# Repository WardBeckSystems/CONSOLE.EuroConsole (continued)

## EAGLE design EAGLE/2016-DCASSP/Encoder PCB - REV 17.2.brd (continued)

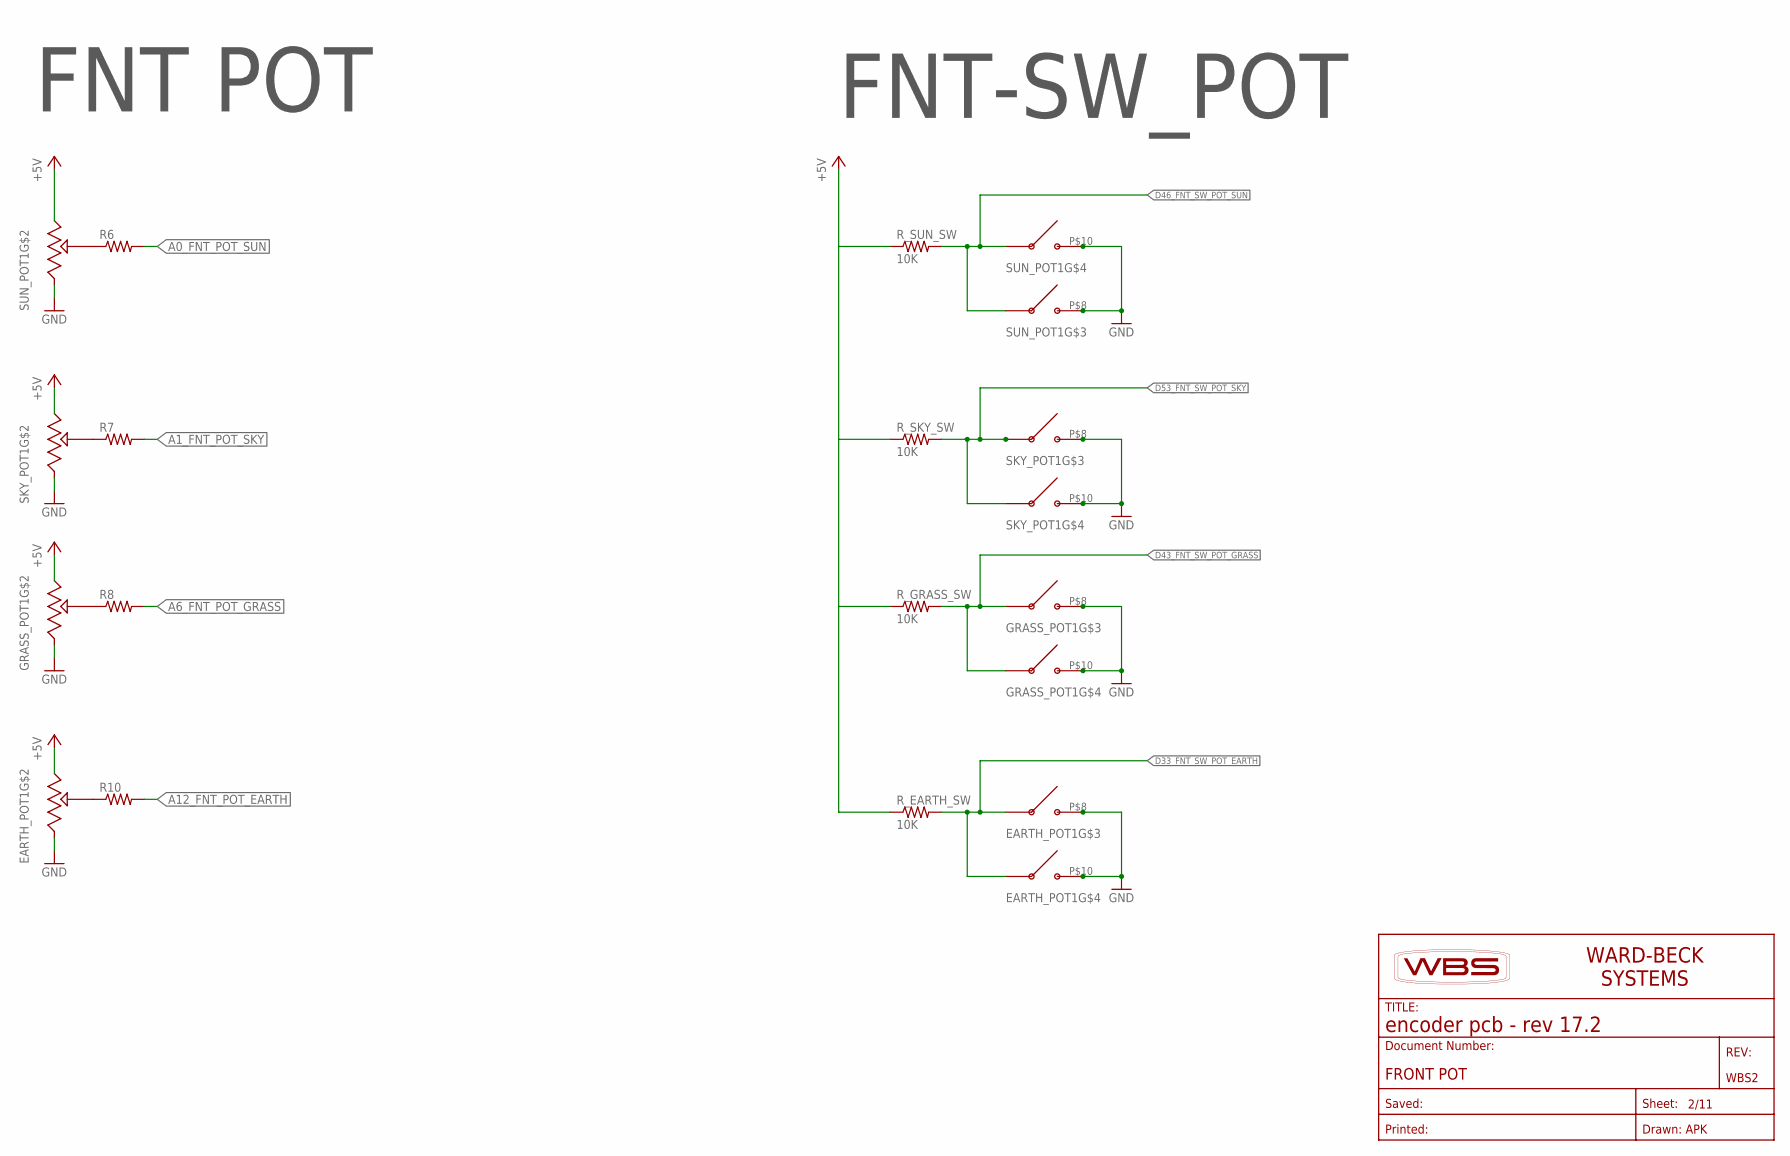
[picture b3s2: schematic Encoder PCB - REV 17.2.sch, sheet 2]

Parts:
EARTH_POT1: WBS_10-081_DUALPOT+DUALSWITCH; WBS_10-081
GRASS_POT1: WBS_10-081_DUALPOT+DUALSWITCH; WBS_10-081
R6, R7, R8, R10: R-US_0309/12; 0309/12
R_EARTH_SW: 10K; M0805
R_GRASS_SW: 10K; M0805
R_SKY_SW: 10K; M0805
R_SUN_SW: 10K; M0805
SKY_POT1: WBS_10-081_DUALPOT+DUALSWITCH; WBS_10-081
SUN_POT1: WBS_10-081_DUALPOT+DUALSWITCH; WBS_10-081
WBS2: FRONT POT; WBS-FRAME_PCB

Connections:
+5V: EARTH_POT1.P$6 (CW), GRASS_POT1.P$6 (CW), R_EARTH_SW.1, R_GRASS_SW.1, R_SKY_SW.1, R_SUN_SW.1, SKY_POT1.P$6 (CW), SUN_POT1.P$6 (CW); also elsewhere on the board
A0_FNT_POT_SUN: R6.2; also elsewhere on the board
A1_FNT_POT_SKY: R7.2; also elsewhere on the board
A6_FNT_POT_GRASS: R8.2; also elsewhere on the board
A12_FNT_POT_EARTH: R10.2; also elsewhere on the board
D33_FNT_SW_POT_EARTH: EARTH_POT1.P$7, EARTH_POT1.P$9, R_EARTH_SW.2; also elsewhere on the board
D43_FNT_SW_POT_GRASS: GRASS_POT1.P$7, GRASS_POT1.P$9, R_GRASS_SW.2; also elsewhere on the board
D46_FNT_SW_POT_SUN: R_SUN_SW.2, SUN_POT1.P$7, SUN_POT1.P$9; also elsewhere on the board
D53_FNT_SW_POT_SKY: R_SKY_SW.2, SKY_POT1.P$7, SKY_POT1.P$9; also elsewhere on the board
GND: EARTH_POT1.P$4 (CCW), EARTH_POT1.P$8, EARTH_POT1.P$10, GRASS_POT1.P$4 (CCW), GRASS_POT1.P$8, GRASS_POT1.P$10, SKY_POT1.P$4 (CCW), SKY_POT1.P$8, SKY_POT1.P$10, SUN_POT1.P$4 (CCW), SUN_POT1.P$8, SUN_POT1.P$10; also elsewhere on the board
unnamed: EARTH_POT1.P$5 (WIPER), R10.1
unnamed: R7.1, SKY_POT1.P$5 (WIPER)
unnamed: R6.1, SUN_POT1.P$5 (WIPER)
unnamed: GRASS_POT1.P$5 (WIPER), R8.1

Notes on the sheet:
FNT POT
FNT-SW_POT

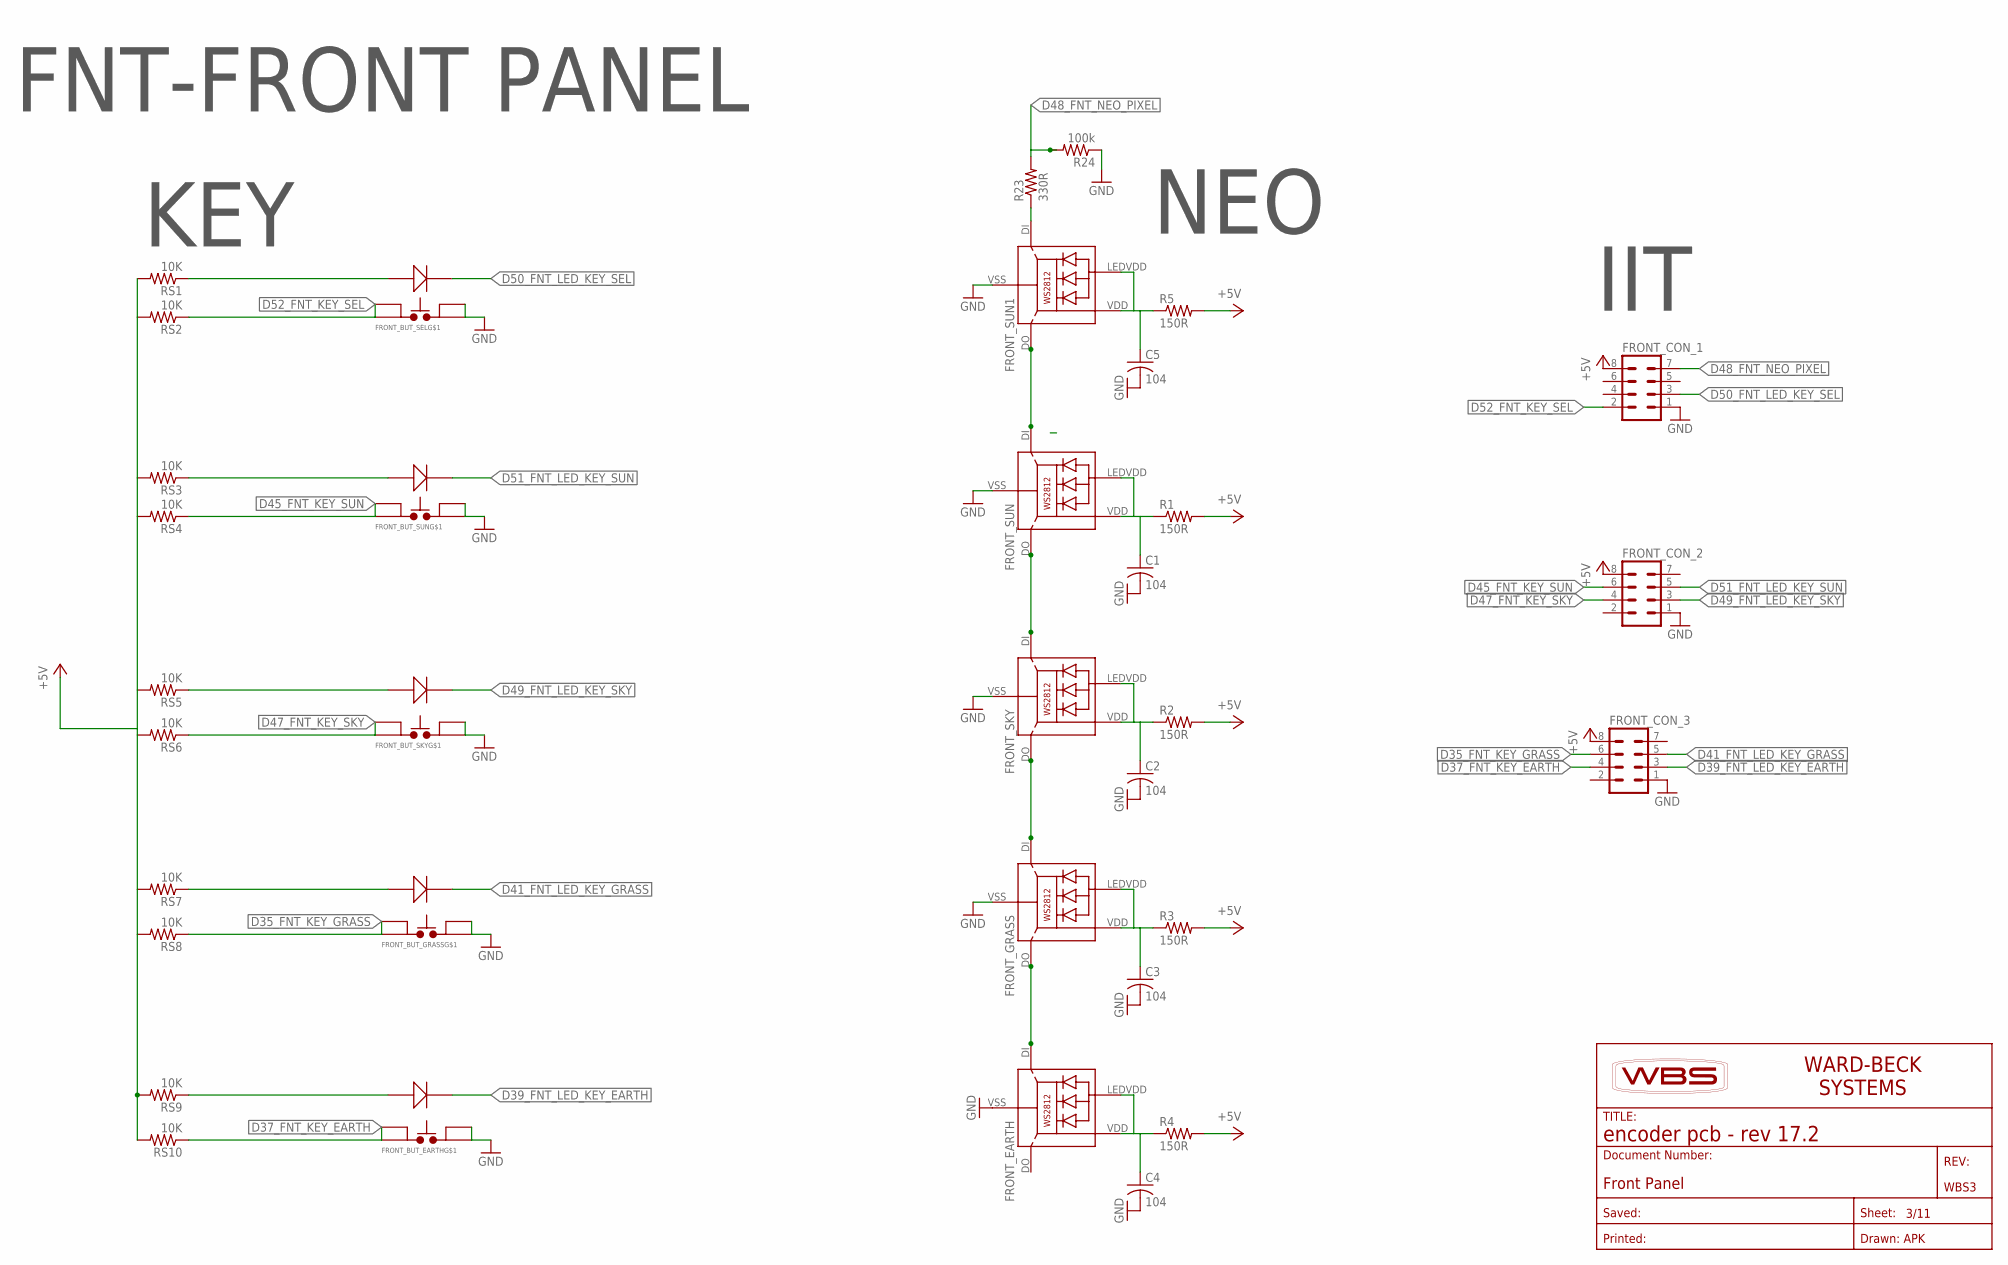
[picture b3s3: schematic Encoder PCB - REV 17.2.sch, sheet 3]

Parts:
C1, C2, C3, C4, C5: 104; C0805
FRONT_BUT_EARTH: SWITCH-POD-BUTTON_WITH_LED; SWITCH-PODBUTTON
FRONT_BUT_GRASS: SWITCH-POD-BUTTON_WITH_LED; SWITCH-PODBUTTON
FRONT_BUT_SEL: SWITCH-POD-BUTTON_WITH_LED; SWITCH-PODBUTTON
FRONT_BUT_SKY: SWITCH-POD-BUTTON_WITH_LED; SWITCH-PODBUTTON
FRONT_BUT_SUN: SWITCH-POD-BUTTON_WITH_LED; SWITCH-PODBUTTON
FRONT_CON_1, FRONT_CON_2, FRONT_CON_3: MA04-2
FRONT_EARTH: WS2812
FRONT_GRASS: WS2812
FRONT_SKY: WS2812
FRONT_SUN, FRONT_SUN1: WS2812
R1, R2, R3, R4, R5: 150R; M0805
R23: 330R; M0805
R24: 100k; M0805
RS1, RS2, RS3, RS4, RS5, RS6, RS7, RS8, RS9, RS10: 10K; M0805
WBS3: Front Panel; WBS-FRAME_PCB

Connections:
+5V: FRONT_CON_1.8, FRONT_CON_2.8, FRONT_CON_3.8, R1.2, R2.2, R3.2, R4.2, R5.2, RS1.2, RS2.2, RS3.2, RS4.2, RS5.2, RS6.2, RS7.2, RS8.2, RS9.2, RS10.2; also elsewhere on the board
D35_FNT_KEY_GRASS: FRONT_BUT_GRASS.SW1A, FRONT_BUT_GRASS.SW2A, FRONT_CON_3.6, RS8.1; also elsewhere on the board
D37_FNT_KEY_EARTH: FRONT_BUT_EARTH.SW1A, FRONT_BUT_EARTH.SW2A, FRONT_CON_3.4, RS10.1; also elsewhere on the board
D39_FNT_LED_KEY_EARTH: FRONT_BUT_EARTH.LEDB, FRONT_CON_3.3; also elsewhere on the board
D41_FNT_LED_KEY_GRASS: FRONT_BUT_GRASS.LEDB, FRONT_CON_3.5; also elsewhere on the board
D45_FNT_KEY_SUN: FRONT_BUT_SUN.SW1A, FRONT_BUT_SUN.SW2A, FRONT_CON_2.6, RS4.1; also elsewhere on the board
D47_FNT_KEY_SKY: FRONT_BUT_SKY.SW1A, FRONT_BUT_SKY.SW2A, FRONT_CON_2.4, RS6.1; also elsewhere on the board
D48_FNT_NEO_PIXEL: FRONT_CON_1.7, R23.2, R24.2; also elsewhere on the board
D49_FNT_LED_KEY_SKY: FRONT_BUT_SKY.LEDB, FRONT_CON_2.3; also elsewhere on the board
D50_FNT_LED_KEY_SEL: FRONT_BUT_SEL.LEDB, FRONT_CON_1.3; also elsewhere on the board
D51_FNT_LED_KEY_SUN: FRONT_BUT_SUN.LEDB, FRONT_CON_2.5; also elsewhere on the board
D52_FNT_KEY_SEL: FRONT_BUT_SEL.SW1A, FRONT_BUT_SEL.SW2A, FRONT_CON_1.2, RS2.1; also elsewhere on the board
GND: C1.2, C2.2, C3.2, C4.2, C5.2, FRONT_BUT_EARTH.SW1B, FRONT_BUT_EARTH.SW2B, FRONT_BUT_GRASS.SW1B, FRONT_BUT_GRASS.SW2B, FRONT_BUT_SEL.SW1B, FRONT_BUT_SEL.SW2B, FRONT_BUT_SKY.SW1B, FRONT_BUT_SKY.SW2B, FRONT_BUT_SUN.SW1B, FRONT_BUT_SUN.SW2B, FRONT_CON_1.1, FRONT_CON_2.1, FRONT_CON_3.1, FRONT_EARTH.VSS (GND), FRONT_GRASS.VSS (GND), FRONT_SKY.VSS (GND), FRONT_SUN.VSS (GND), FRONT_SUN1.VSS (GND), R24.1; also elsewhere on the board
unnamed: FRONT_BUT_GRASS.LEDA, RS7.1
unnamed: FRONT_BUT_SKY.LEDA, RS5.1
unnamed: C1.1, FRONT_SUN.LEDVDD, FRONT_SUN.VDD, R1.1
unnamed: FRONT_BUT_SUN.LEDA, RS3.1
unnamed: FRONT_BUT_SEL.LEDA, RS1.1
unnamed: FRONT_GRASS.DI, FRONT_SKY.DO
unnamed: C2.1, FRONT_SKY.LEDVDD, FRONT_SKY.VDD, R2.1
unnamed: FRONT_BUT_EARTH.LEDA, RS9.1
unnamed: C3.1, FRONT_GRASS.LEDVDD, FRONT_GRASS.VDD, R3.1
unnamed: FRONT_SUN.DI, FRONT_SUN1.DO
unnamed: C4.1, FRONT_EARTH.LEDVDD, FRONT_EARTH.VDD, R4.1
unnamed: C5.1, FRONT_SUN1.LEDVDD, FRONT_SUN1.VDD, R5.1
unnamed: FRONT_EARTH.DI, FRONT_GRASS.DO, FRONT_SKY.DI, FRONT_SUN.DO
unnamed: FRONT_SUN1.DI, R23.1

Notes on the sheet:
FNT-FRONT PANEL
KEY
NEO
IIT

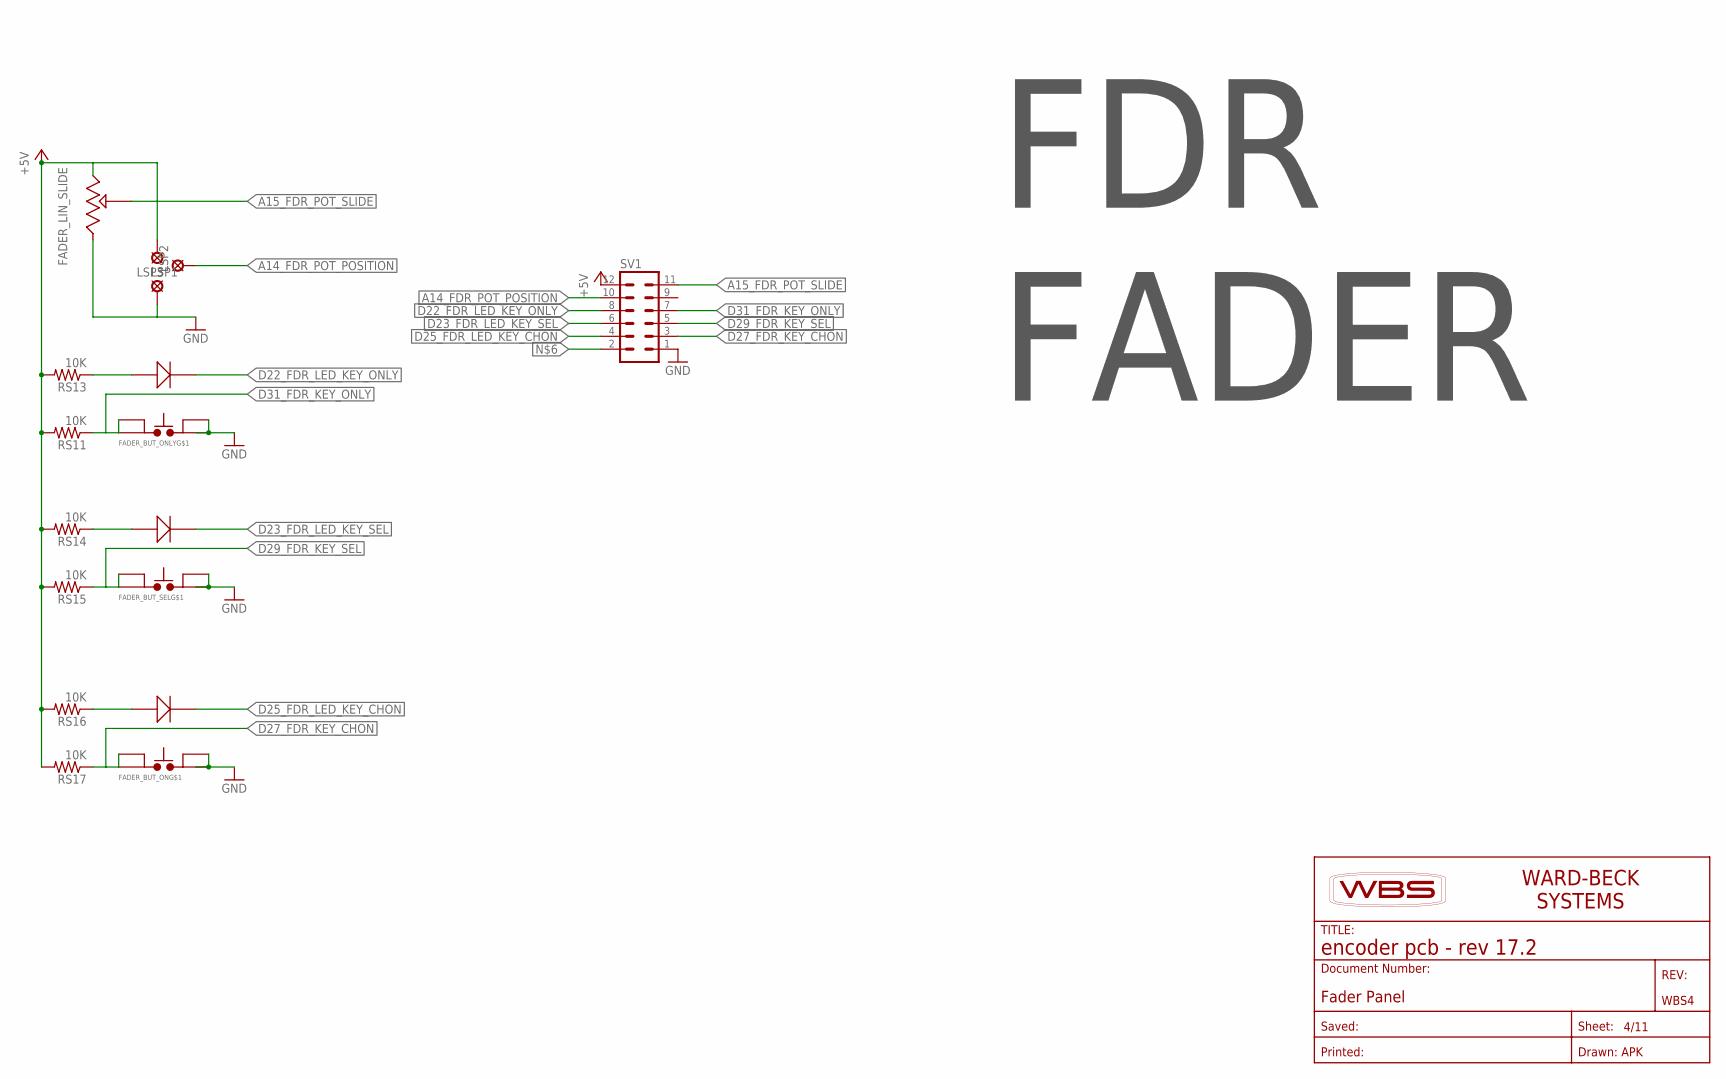
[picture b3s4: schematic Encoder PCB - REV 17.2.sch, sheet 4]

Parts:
FADER_BUT_ON: SWITCH-POD-BUTTON_WITH_LED; SWITCH-PODBUTTON
FADER_BUT_ONLY: SWITCH-POD-BUTTON_WITH_LED; SWITCH-PODBUTTON
FADER_BUT_SEL: SWITCH-POD-BUTTON_WITH_LED; SWITCH-PODBUTTON
FADER_LIN_SLIDE: BOURNS-PTA6043_SLIDEPOT
LSP1, LSP2, LSP3: MCS10B
RS11, RS13, RS14, RS15, RS16, RS17: 10K; M0805
SV1: MA06-2
WBS4: Fader Panel; WBS-FRAME_PCB

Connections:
+5V: FADER_LIN_SLIDE.P$3 (CW), LSP3.MP, RS11.2, RS13.2, RS14.2, RS15.2, RS16.2, RS17.2, SV1.12; also elsewhere on the board
A14_FDR_POT_POSITION: LSP2.MP, SV1.10; also elsewhere on the board
A15_FDR_POT_SLIDE: FADER_LIN_SLIDE.P$2 (WIPER), SV1.11; also elsewhere on the board
D22_FDR_LED_KEY_ONLY: FADER_BUT_ONLY.LEDB, SV1.8; also elsewhere on the board
D23_FDR_LED_KEY_SEL: FADER_BUT_SEL.LEDB, SV1.6; also elsewhere on the board
D25_FDR_LED_KEY_CHON: FADER_BUT_ON.LEDB, SV1.4; also elsewhere on the board
D27_FDR_KEY_CHON: FADER_BUT_ON.SW1A, FADER_BUT_ON.SW2A, RS17.1, SV1.3; also elsewhere on the board
D29_FDR_KEY_SEL: FADER_BUT_SEL.SW1A, FADER_BUT_SEL.SW2A, RS15.1, SV1.5; also elsewhere on the board
D31_FDR_KEY_ONLY: FADER_BUT_ONLY.SW1A, FADER_BUT_ONLY.SW2A, RS11.1, SV1.7; also elsewhere on the board
GND: FADER_BUT_ON.SW1B, FADER_BUT_ON.SW2B, FADER_BUT_ONLY.SW1B, FADER_BUT_ONLY.SW2B, FADER_BUT_SEL.SW1B, FADER_BUT_SEL.SW2B, FADER_LIN_SLIDE.P$1 (CCW), LSP1.MP, SV1.1; also elsewhere on the board
unnamed: FADER_BUT_ON.LEDA, RS16.1
unnamed: FADER_BUT_SEL.LEDA, RS14.1
unnamed: FADER_BUT_ONLY.LEDA, RS13.1
unnamed 67: SV1.2; also elsewhere on the board

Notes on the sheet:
FDR FADER

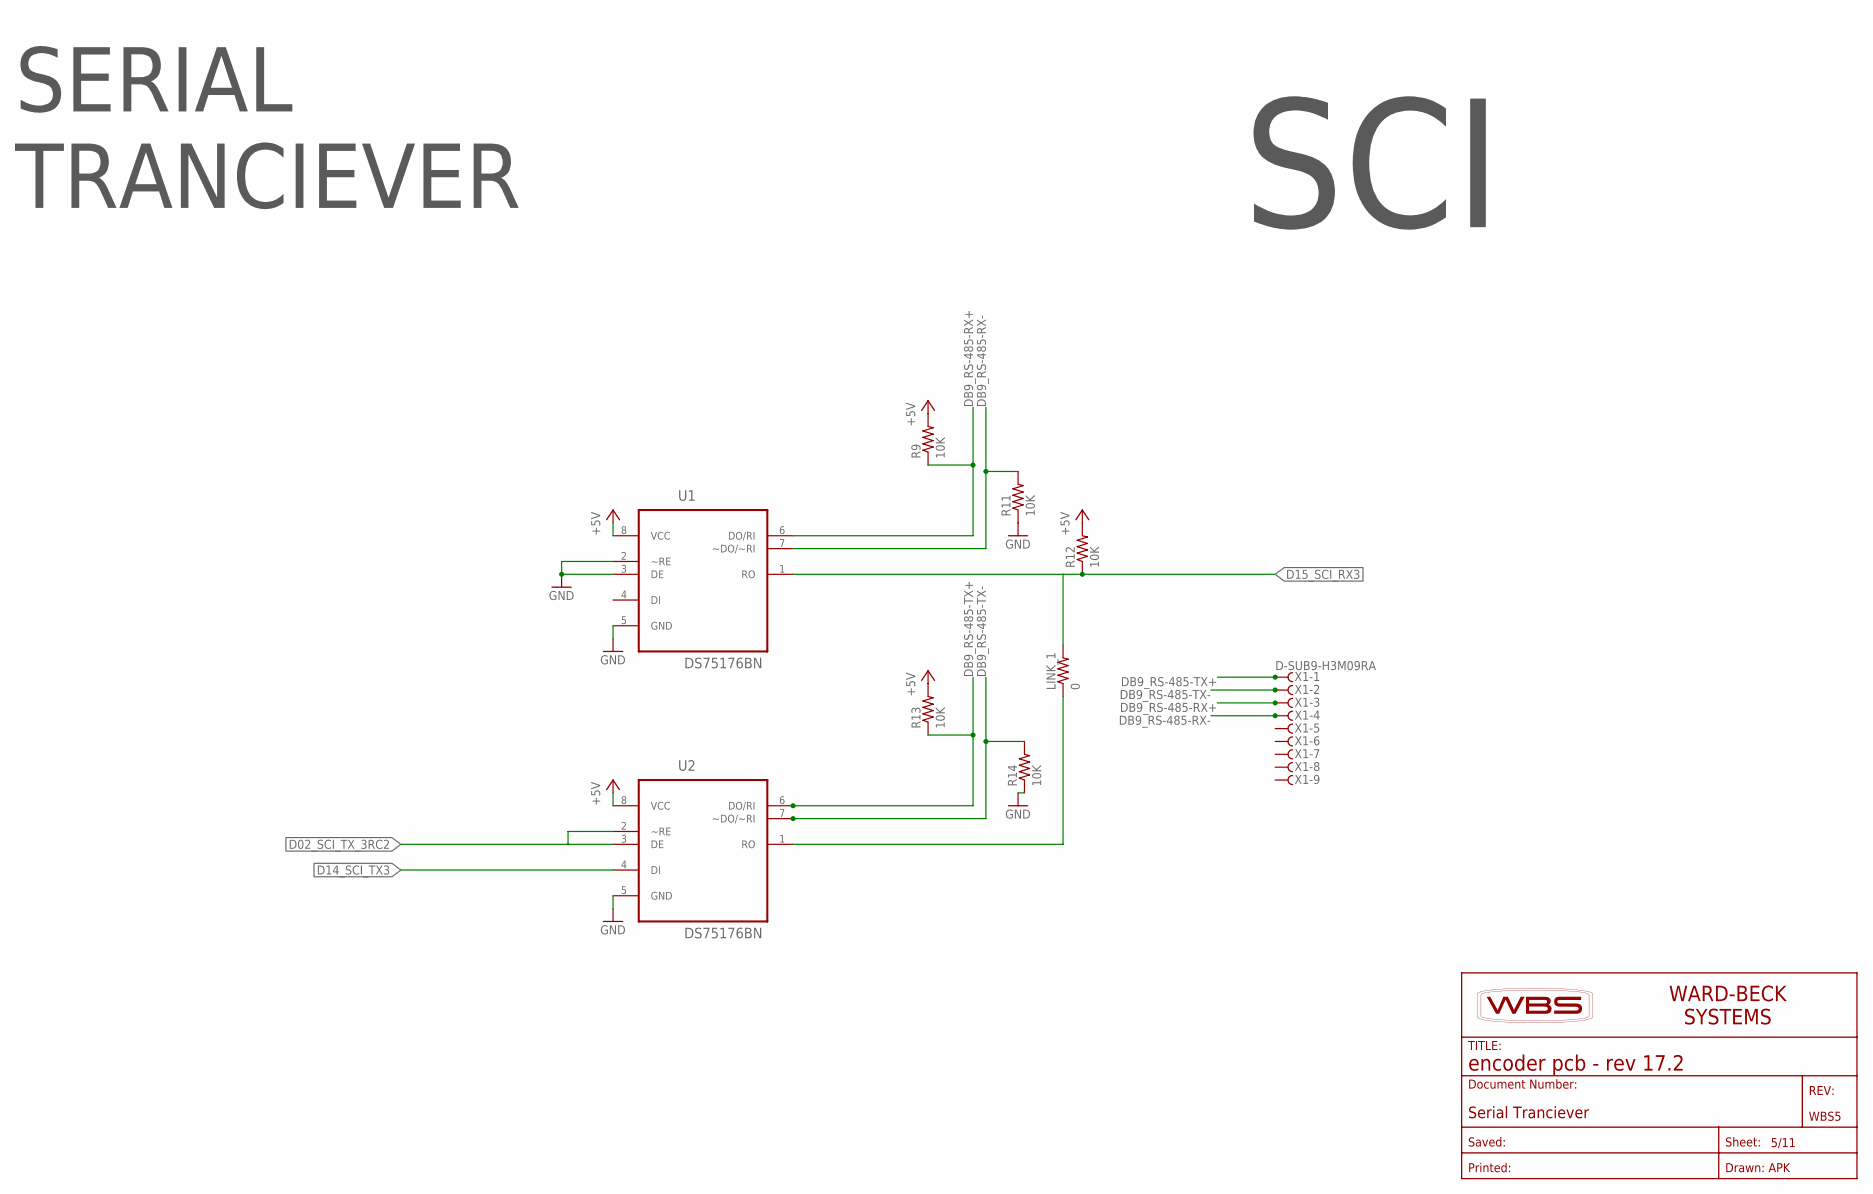
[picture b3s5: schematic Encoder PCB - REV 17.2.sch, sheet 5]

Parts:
LINK_1: 0; M0805
R9, R11, R12, R13, R14: 10K; M0805
U1, U2: DS75176BN; DIP254P762X508-8
WBS5: Serial Tranciever; WBS-FRAME_PCB
X1: D-SUB9-H3M09RA; H3M09RA

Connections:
+5V: R9.2, R12.2, R13.2, U1.8 (VCC), U2.8 (VCC); also elsewhere on the board
D02_SCI_TX_3RC2: U2.2 (~RE), U2.3 (DE); also elsewhere on the board
D14_SCI_TX3: U2.4 (DI); also elsewhere on the board
D15_SCI_RX3: LINK_1.2, R12.1, U1.1 (RO); also elsewhere on the board
DB9_RS-485-RX+: R9.1, U1.6 (DO/RI), X1.3
DB9_RS-485-RX-: R11.2, U1.7 (~DO/~RI), X1.4
DB9_RS-485-TX+: R13.1, U2.6 (DO/RI), X1.1
DB9_RS-485-TX-: R14.2, U2.7 (~DO/~RI), X1.2
GND: R11.1, R14.1, U1.2 (~RE), U1.3 (DE), U1.5 (GND), U2.5 (GND); also elsewhere on the board
unnamed: LINK_1.1, U2.1 (RO)

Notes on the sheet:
SERIAL TRANCIEVER
SCI

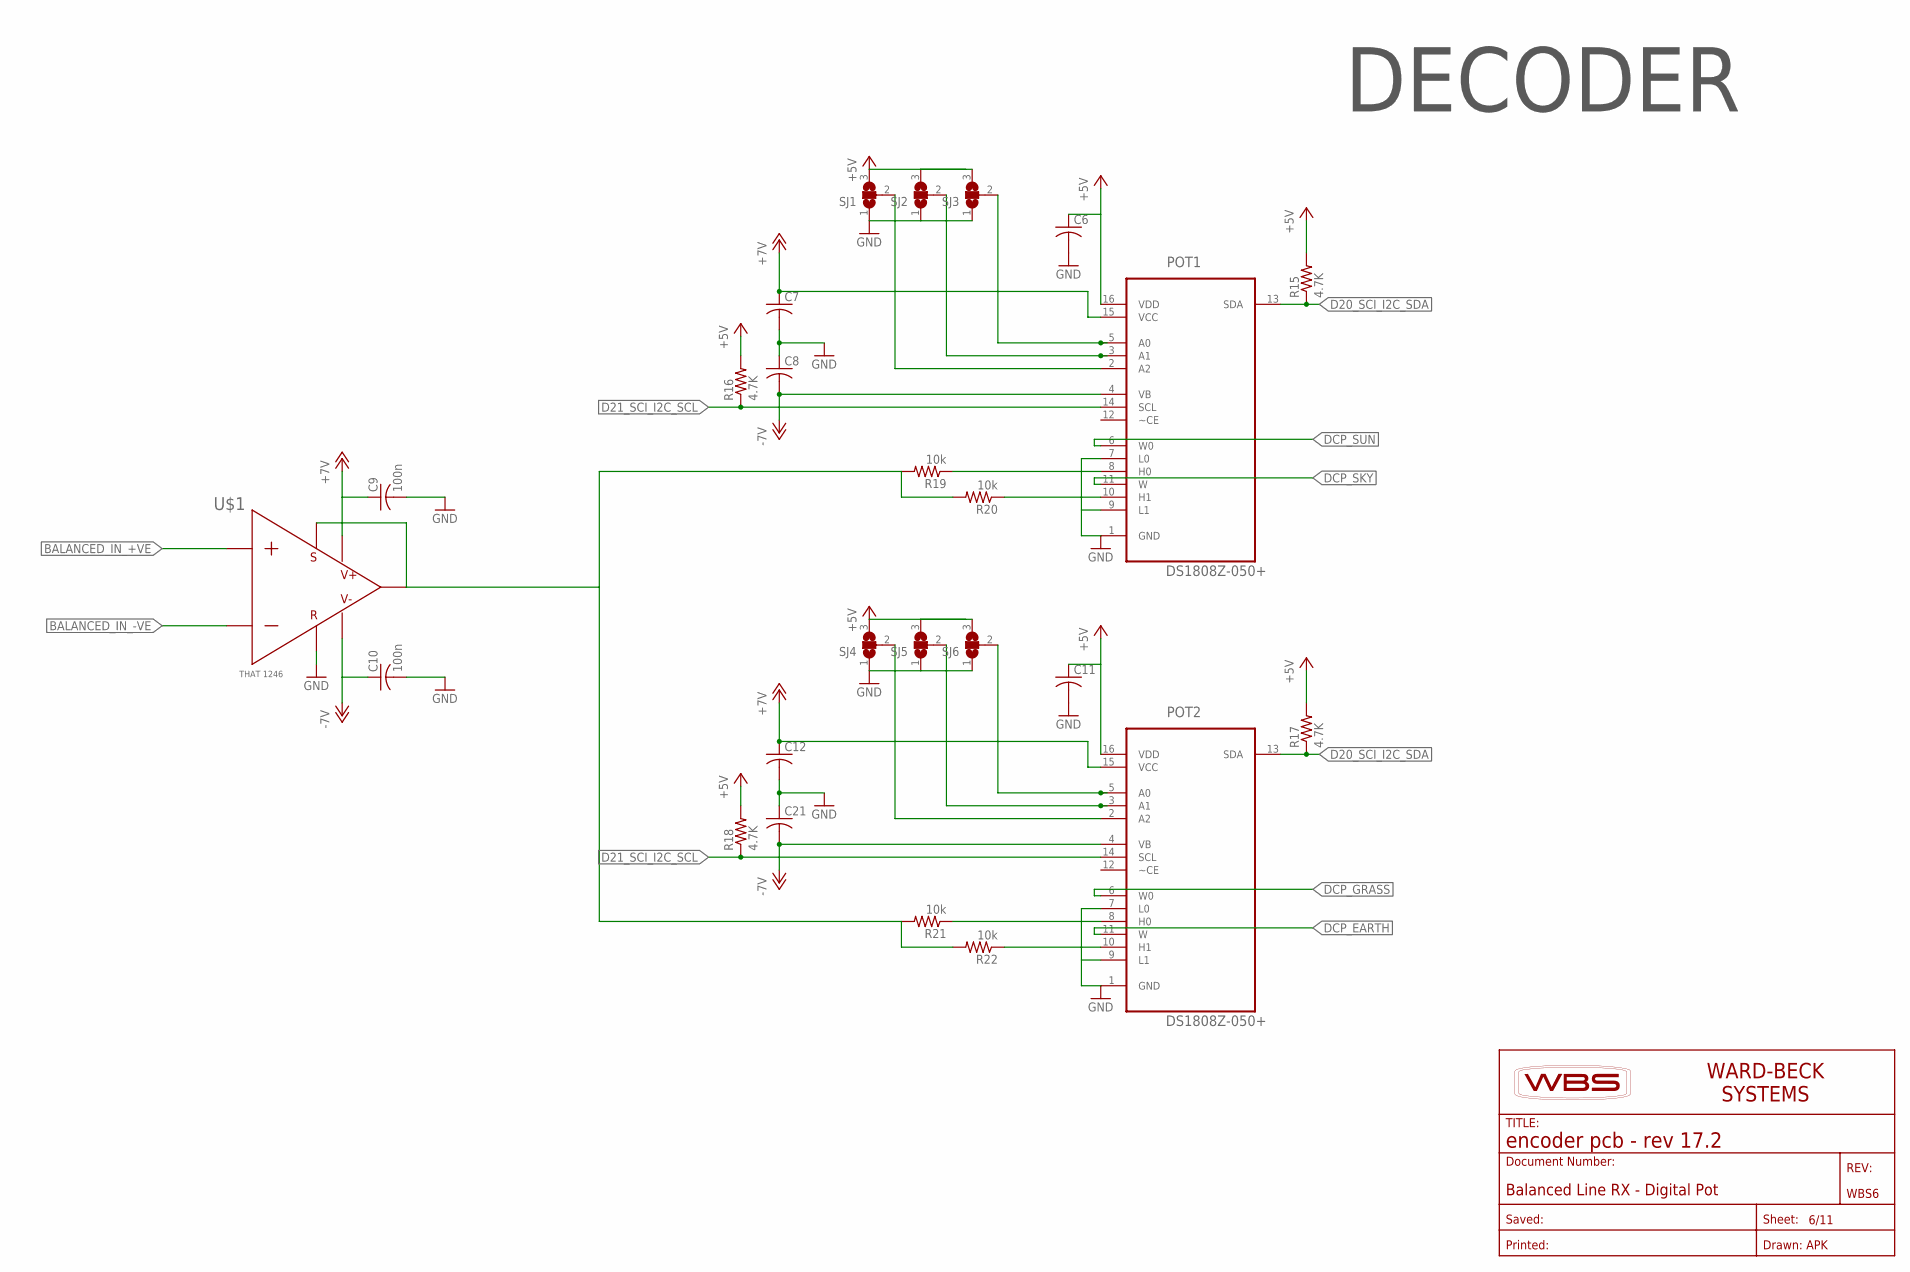
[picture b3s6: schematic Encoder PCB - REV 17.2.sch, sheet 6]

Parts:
C6, C7, C8, C11, C12, C21: C-USC0805; C0805
C9, C10: 100n; C0805
POT1, POT2: DS1808Z-050+; SOIC127P600X175-16N
R15, R16, R17, R18: 4.7K; M0805
R19, R20, R21, R22: 10k; M0805
SJ1, SJ2, SJ3, SJ4, SJ5, SJ6: SJ2W; SJ_2
U$1: OPAMP-THAT1246_LINE_RECEIVER; DIP8
WBS6: Balanced Line RX - Digital Pot; WBS-FRAME_PCB

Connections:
+5V: C6.1, C11.1, POT1.16 (VDD), POT2.16 (VDD), R15.2, R16.2, R17.2, R18.2, SJ1.3, SJ2.3, SJ3.3, SJ4.3, SJ5.3, SJ6.3; also elsewhere on the board
+12V: C7.1, C9.1, C12.1, POT1.15 (VCC), POT2.15 (VCC), U$1.P$7 (V+); also elsewhere on the board
-12V: C8.2, C10.1, C21.2, POT1.4 (VB), POT2.4 (VB), U$1.P$4 (V-); also elsewhere on the board
BALANCED_IN_+VE: U$1.P$3 (IN+)
BALANCED_IN_-VE: U$1.P$2 (IN-)
D20_SCI_I2C_SDA: POT1.13 (SDA), POT2.13 (SDA), R15.1, R17.1; also elsewhere on the board
D21_SCI_I2C_SCL: POT1.14 (SCL), POT2.14 (SCL), R16.1, R18.1; also elsewhere on the board
DCP_EARTH: POT2.11 (W); also elsewhere on the board
DCP_GRASS: POT2.6 (W0); also elsewhere on the board
DCP_SKY: POT1.11 (W); also elsewhere on the board
DCP_SUN: POT1.6 (W0); also elsewhere on the board
GND: C6.2, C9.2, C10.2, C11.2, POT1.1 (GND), POT1.7 (L0), POT1.9 (L1), POT2.1 (GND), POT2.7 (L0), POT2.9 (L1), SJ1.1, SJ2.1, SJ3.1, SJ4.1, SJ5.1, SJ6.1, U$1.P$1 (REF); also elsewhere on the board
unnamed: C7.2, C8.1
unnamed: POT1.2 (A2), SJ1.2
unnamed: POT1.3 (A1), SJ2.2
unnamed: POT1.5 (A0), SJ3.2
unnamed: C12.2, C21.1
unnamed: POT2.2 (A2), SJ4.2
unnamed: POT2.3 (A1), SJ5.2
unnamed: POT2.5 (A0), SJ6.2
POT_A1_IN: POT1.8 (H0), POT2.8 (H0), R19.1
POT_B1_IN: POT1.10 (H1), R20.1
POT_B1_IN1: POT2.10 (H1), R22.1
UNBALANCED_OUT: R19.2, R20.2, R21.2, R22.2, U$1.P$5 (SENS), U$1.P$6 (OUT)

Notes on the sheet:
DECODER

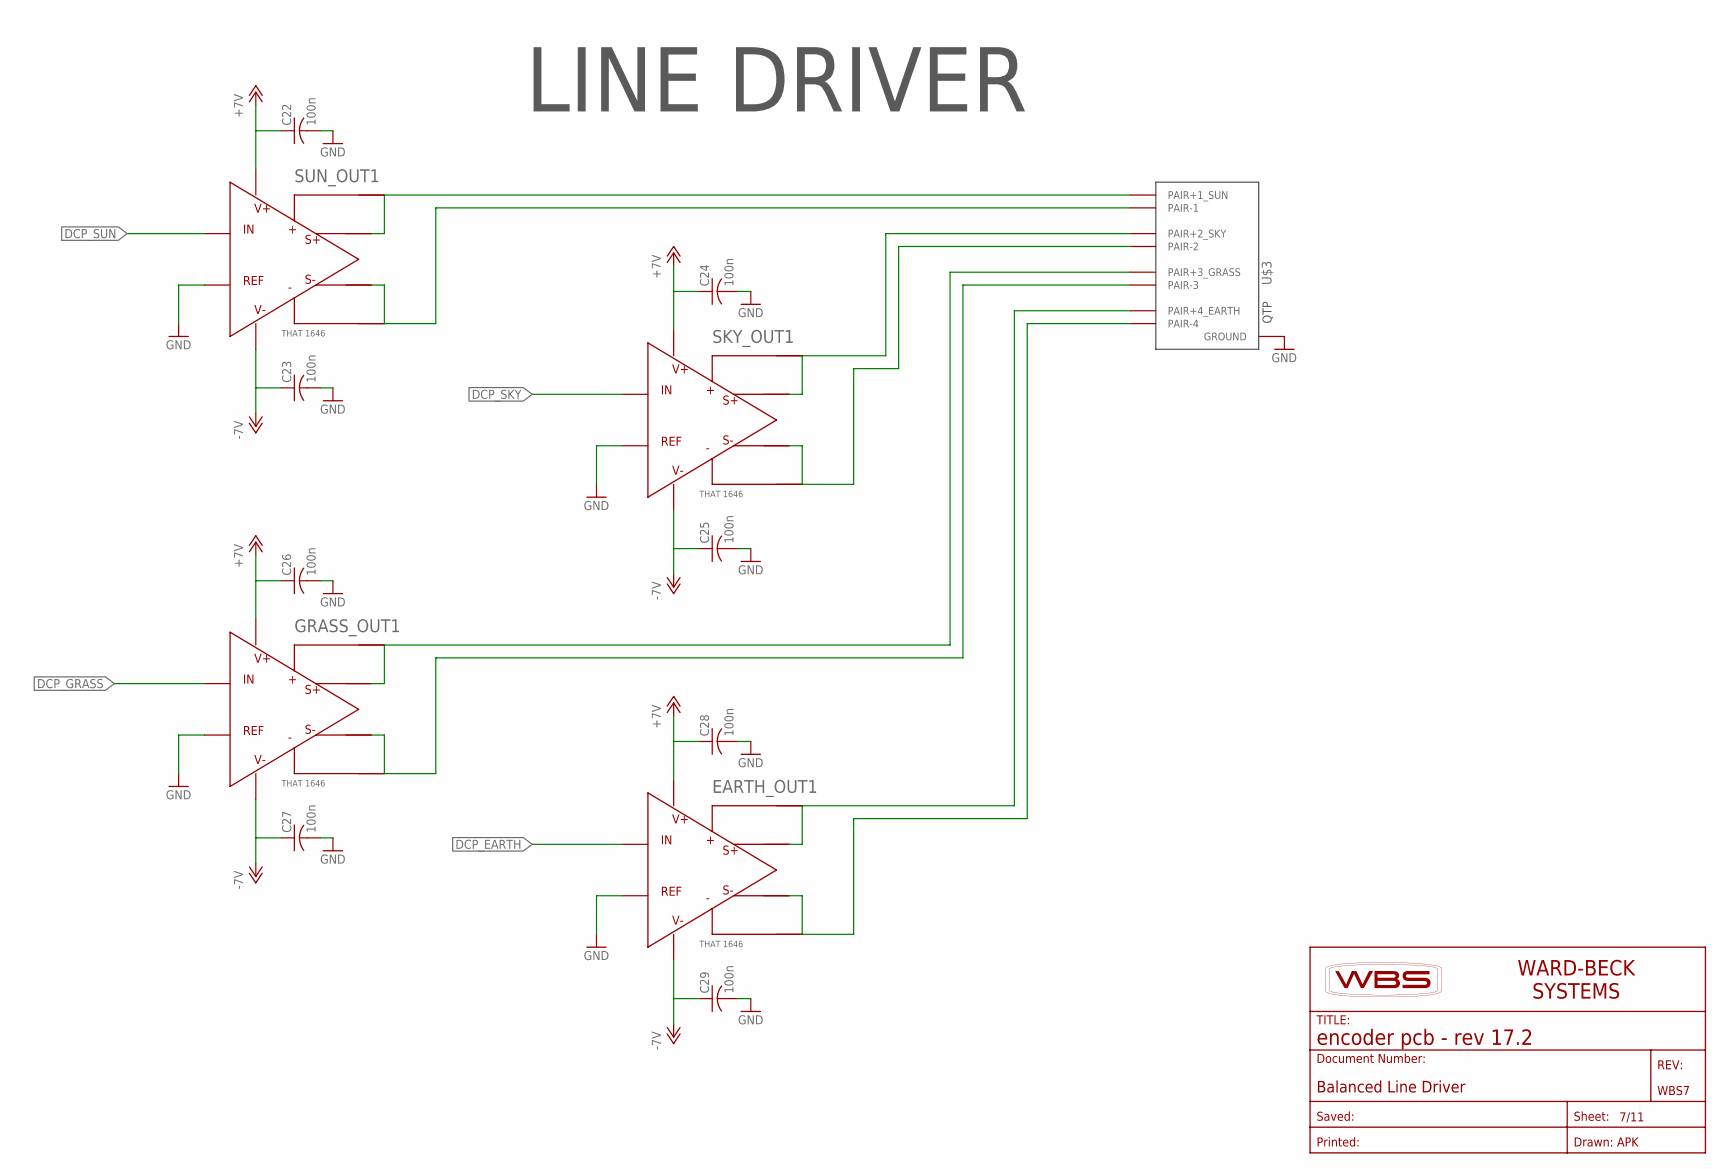
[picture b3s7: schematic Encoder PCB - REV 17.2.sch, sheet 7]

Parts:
C22, C23, C24, C25, C26, C27, C28, C29: 100n; C0805
EARTH_OUT1: OPAMP-THAT1646_LINE_DRIVER; DIP8
GRASS_OUT1: OPAMP-THAT1646_LINE_DRIVER; DIP8
SKY_OUT1: OPAMP-THAT1646_LINE_DRIVER; DIP8
SUN_OUT1: OPAMP-THAT1646_LINE_DRIVER; DIP8
U$3: CON-QTP; ASSMAN-RJ45
WBS7: Balanced Line Driver; WBS-FRAME_PCB

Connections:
+12V: C22.1, C24.1, C26.1, C28.1, EARTH_OUT1.P$6 (V+), GRASS_OUT1.P$6 (V+), SKY_OUT1.P$6 (V+), SUN_OUT1.P$6 (V+); also elsewhere on the board
-12V: C23.1, C25.1, C27.1, C29.1, EARTH_OUT1.P$5 (V-), GRASS_OUT1.P$5 (V-), SKY_OUT1.P$5 (V-), SUN_OUT1.P$5 (V-); also elsewhere on the board
DCP_EARTH: EARTH_OUT1.P$4 (IN); also elsewhere on the board
DCP_GRASS: GRASS_OUT1.P$4 (IN); also elsewhere on the board
DCP_SKY: SKY_OUT1.P$4 (IN); also elsewhere on the board
DCP_SUN: SUN_OUT1.P$4 (IN); also elsewhere on the board
GND: C22.2, C23.2, C24.2, C25.2, C26.2, C27.2, C28.2, C29.2, EARTH_OUT1.P$3 (REF), GRASS_OUT1.P$3 (REF), SKY_OUT1.P$3 (REF), SUN_OUT1.P$3 (REF), U$3.P$9 (GROUND), U$3.P$10 (GROUND), U$3.P$11 (GROUND), U$3.P$12 (GROUND); also elsewhere on the board
unnamed: SUN_OUT1.P$7 (S+), SUN_OUT1.P$8 (OUT+), U$3.P1+ (PAIR+1_SUN)
unnamed: SUN_OUT1.P$1 (OUT-), SUN_OUT1.P$2 (S-), U$3.P1- (PAIR-1)
unnamed: SKY_OUT1.P$7 (S+), SKY_OUT1.P$8 (OUT+), U$3.P2+ (PAIR+2_SKY)
unnamed: SKY_OUT1.P$1 (OUT-), SKY_OUT1.P$2 (S-), U$3.P2- (PAIR-2)
unnamed: EARTH_OUT1.P$1 (OUT-), EARTH_OUT1.P$2 (S-), U$3.P4- (PAIR-4)
unnamed: GRASS_OUT1.P$7 (S+), GRASS_OUT1.P$8 (OUT+), U$3.P3+ (PAIR+3_GRASS)
unnamed: GRASS_OUT1.P$1 (OUT-), GRASS_OUT1.P$2 (S-), U$3.P3- (PAIR-3)
unnamed: EARTH_OUT1.P$7 (S+), EARTH_OUT1.P$8 (OUT+), U$3.P4+ (PAIR+4_EARTH)

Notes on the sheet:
LINE DRIVER
